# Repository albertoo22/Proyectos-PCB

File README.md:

# Proyectos-PCB
 In this folder I will publish my Hardware design projects. Some designed with KiCAD 6.0 and others with Altium Designer

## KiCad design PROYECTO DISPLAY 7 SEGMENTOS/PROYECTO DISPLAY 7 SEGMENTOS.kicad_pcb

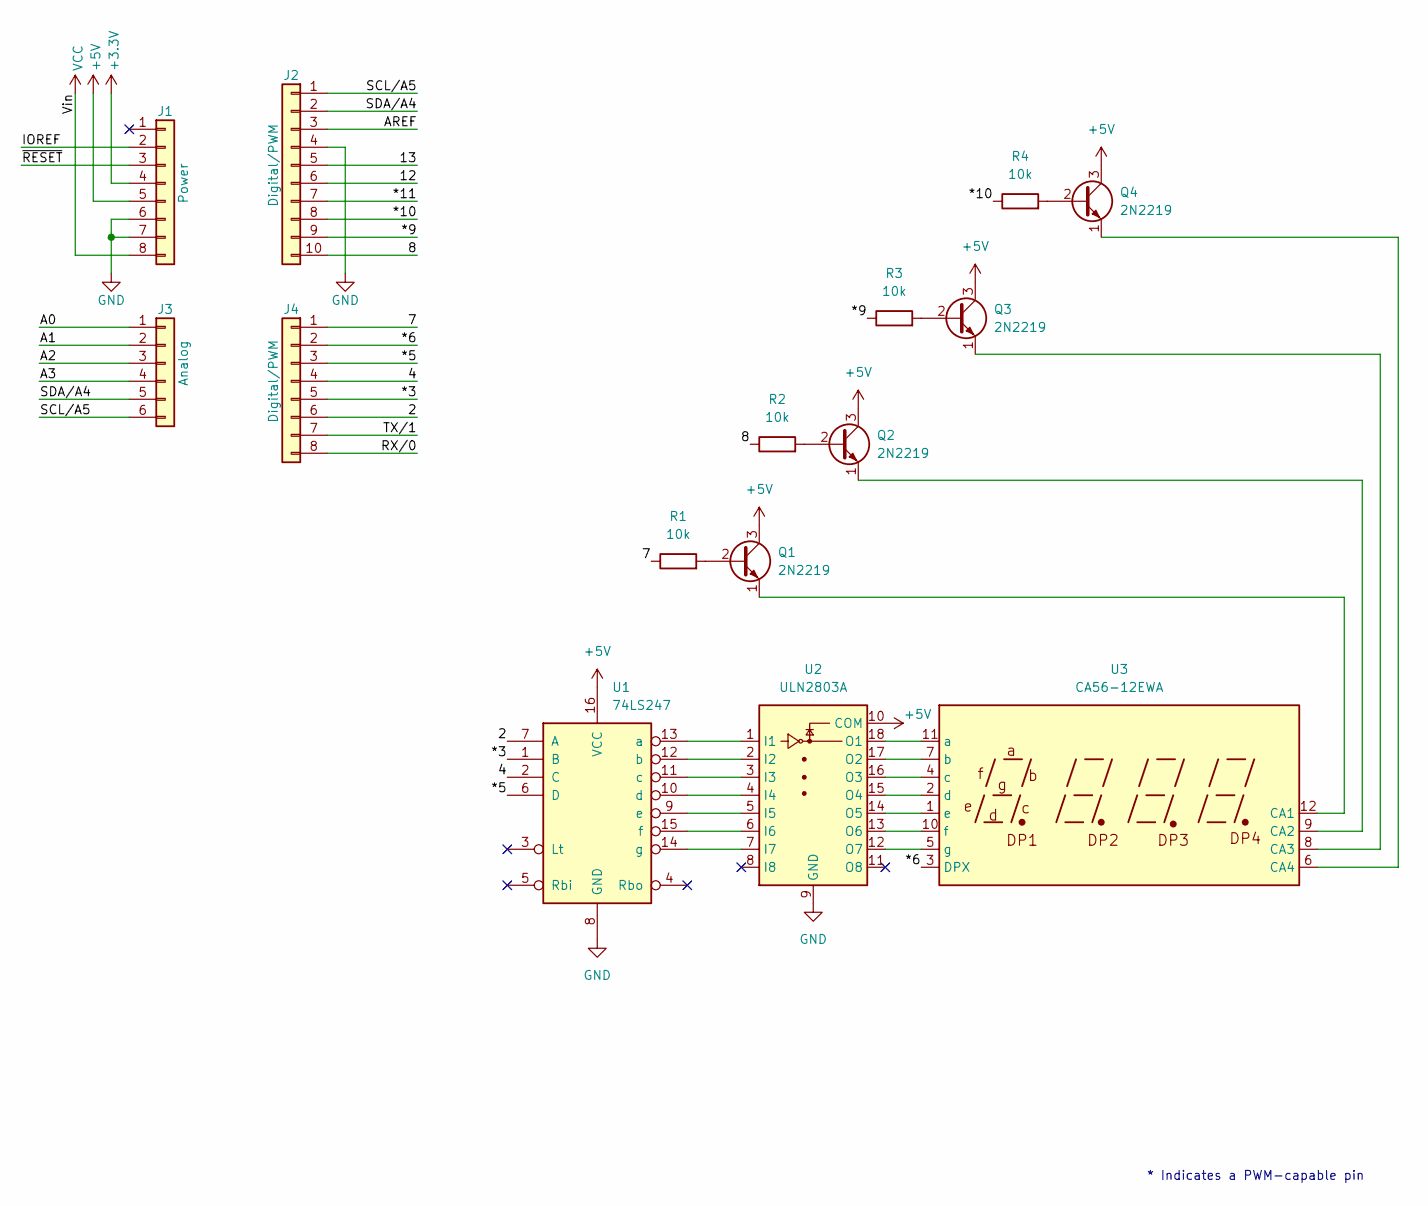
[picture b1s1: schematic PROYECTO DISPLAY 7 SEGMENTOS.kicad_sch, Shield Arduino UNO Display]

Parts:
J1: Power; PinSocket_1x08_P2.54mm_Vertical
J2: Digital/PWM; PinSocket_1x10_P2.54mm_Vertical
J3: Analog; PinSocket_1x06_P2.54mm_Vertical
J4: Digital/PWM; PinSocket_1x08_P2.54mm_Vertical
Q1, Q2, Q3, Q4: 2N2219; TO-39-3
R1, R2, R3, R4: 10k; R_2010_5025Metric
U1: 74LS247; DIP-16_W7.62mm
U2: ULN2803A; DIP-18_W7.62mm
U3: CA56-12EWA

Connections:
+3V3: J1.4
+5V: J1.5, Q1.3 (C), Q2.3 (C), Q3.3 (C), Q4.3 (C), U1.16 (VCC), U2.10 (COM)
/2: J4.6, U1.7 (A)
/4: J4.4, U1.2 (C)
/7: J4.1, R1.1
/8: J2.10, R2.1
/12: J2.6
/13: J2.5
/*3: J4.5, U1.1 (B)
/*5: J4.3, U1.6 (D)
/*6: J4.2, U3.3 (DPX)
/*9: J2.9, R3.1
/*10: J2.8, R4.1
/*11: J2.7
/A0: J3.1
/A1: J3.2
/A2: J3.3
/A3: J3.4
/AREF: J2.3
/IOREF: J1.2
/RX/0: J4.8
/SCL/A5: J2.1, J3.6
/SDA/A4: J2.2, J3.5
/TX/1: J4.7
/~RESET: J1.3
GND: J1.6, J1.7, J2.4, U1.8 (GND), U2.9 (GND)
unnamed: Q1.1 (E), U3.12 (CA1)
unnamed: Q1.2 (B), R1.2
unnamed: Q2.1 (E), U3.9 (CA2)
unnamed: Q2.2 (B), R2.2
unnamed: Q3.1 (E), U3.8 (CA3)
unnamed: Q3.2 (B), R3.2
unnamed: Q4.1 (E), U3.6 (CA4)
unnamed: Q4.2 (B), R4.2
unnamed: U1.9 (e), U2.5 (I5)
unnamed: U1.10 (d), U2.4 (I4)
unnamed: U1.11 (c), U2.3 (I3)
unnamed: U1.12 (b), U2.2 (I2)
unnamed: U1.13 (a), U2.1 (I1)
unnamed: U1.14 (g), U2.7 (I7)
unnamed: U1.15 (f), U2.6 (I6)
unnamed: U2.12 (O7), U3.5 (g)
unnamed: U2.13 (O6), U3.10 (f)
unnamed: U2.14 (O5), U3.1 (e)
unnamed: U2.15 (O4), U3.2 (d)
unnamed: U2.16 (O3), U3.4 (c)
unnamed: U2.17 (O2), U3.7 (b)
unnamed: U2.18 (O1), U3.11 (a)
VCC: J1.8

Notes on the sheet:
* Indicates a PWM-capable pin

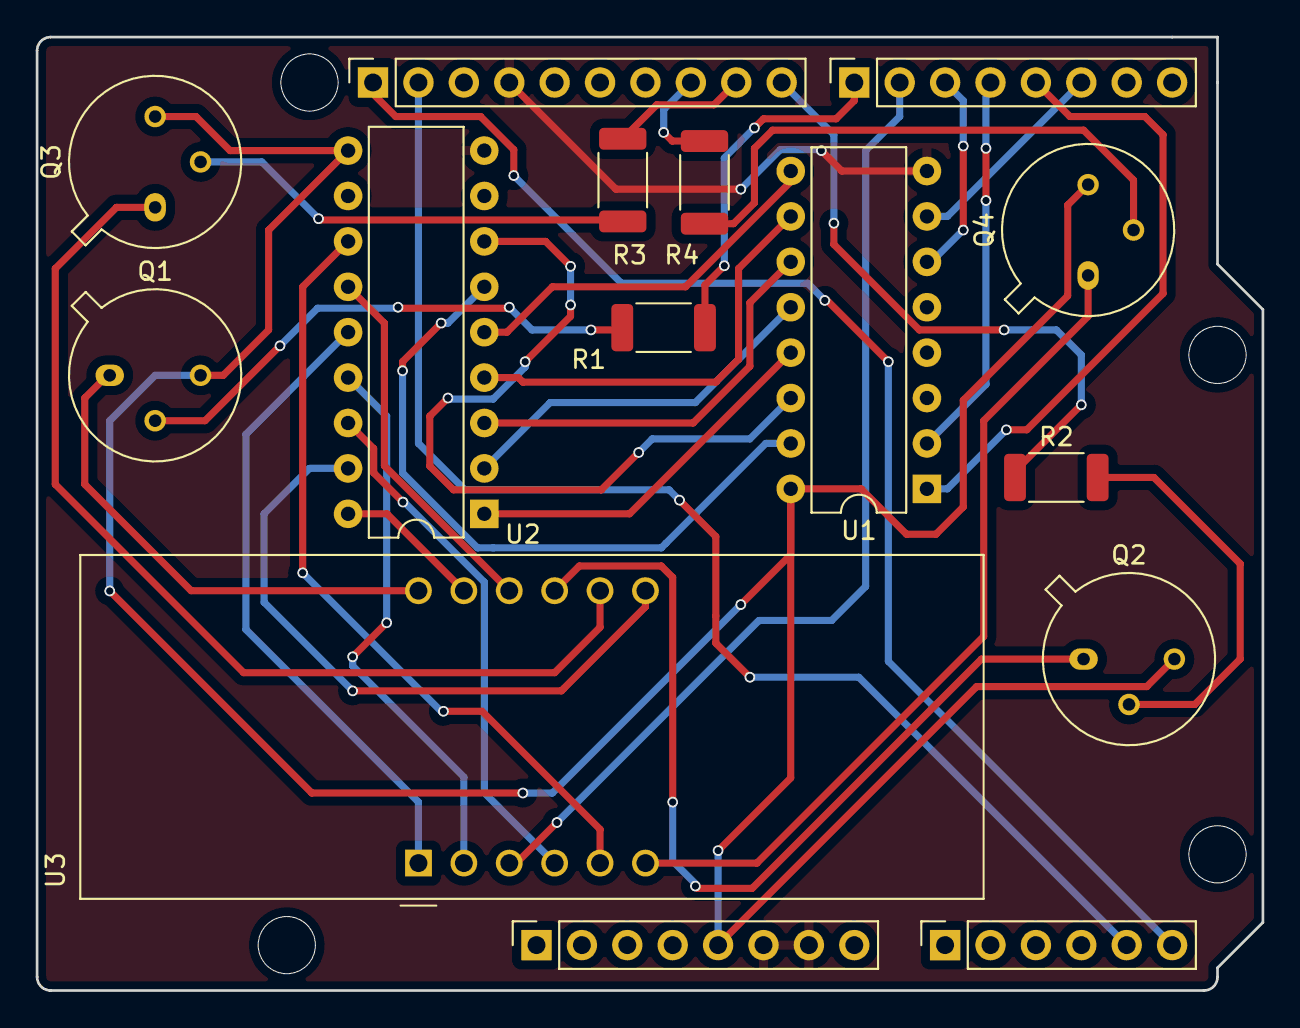
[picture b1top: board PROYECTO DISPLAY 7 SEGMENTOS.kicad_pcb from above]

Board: 2 copper layers, 68.6 x 53.3 mm, 19 parts (0 on the bottom side), 35 nets.

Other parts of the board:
MH1, MH2, MH3, MH4: MountingHole_3.2mm

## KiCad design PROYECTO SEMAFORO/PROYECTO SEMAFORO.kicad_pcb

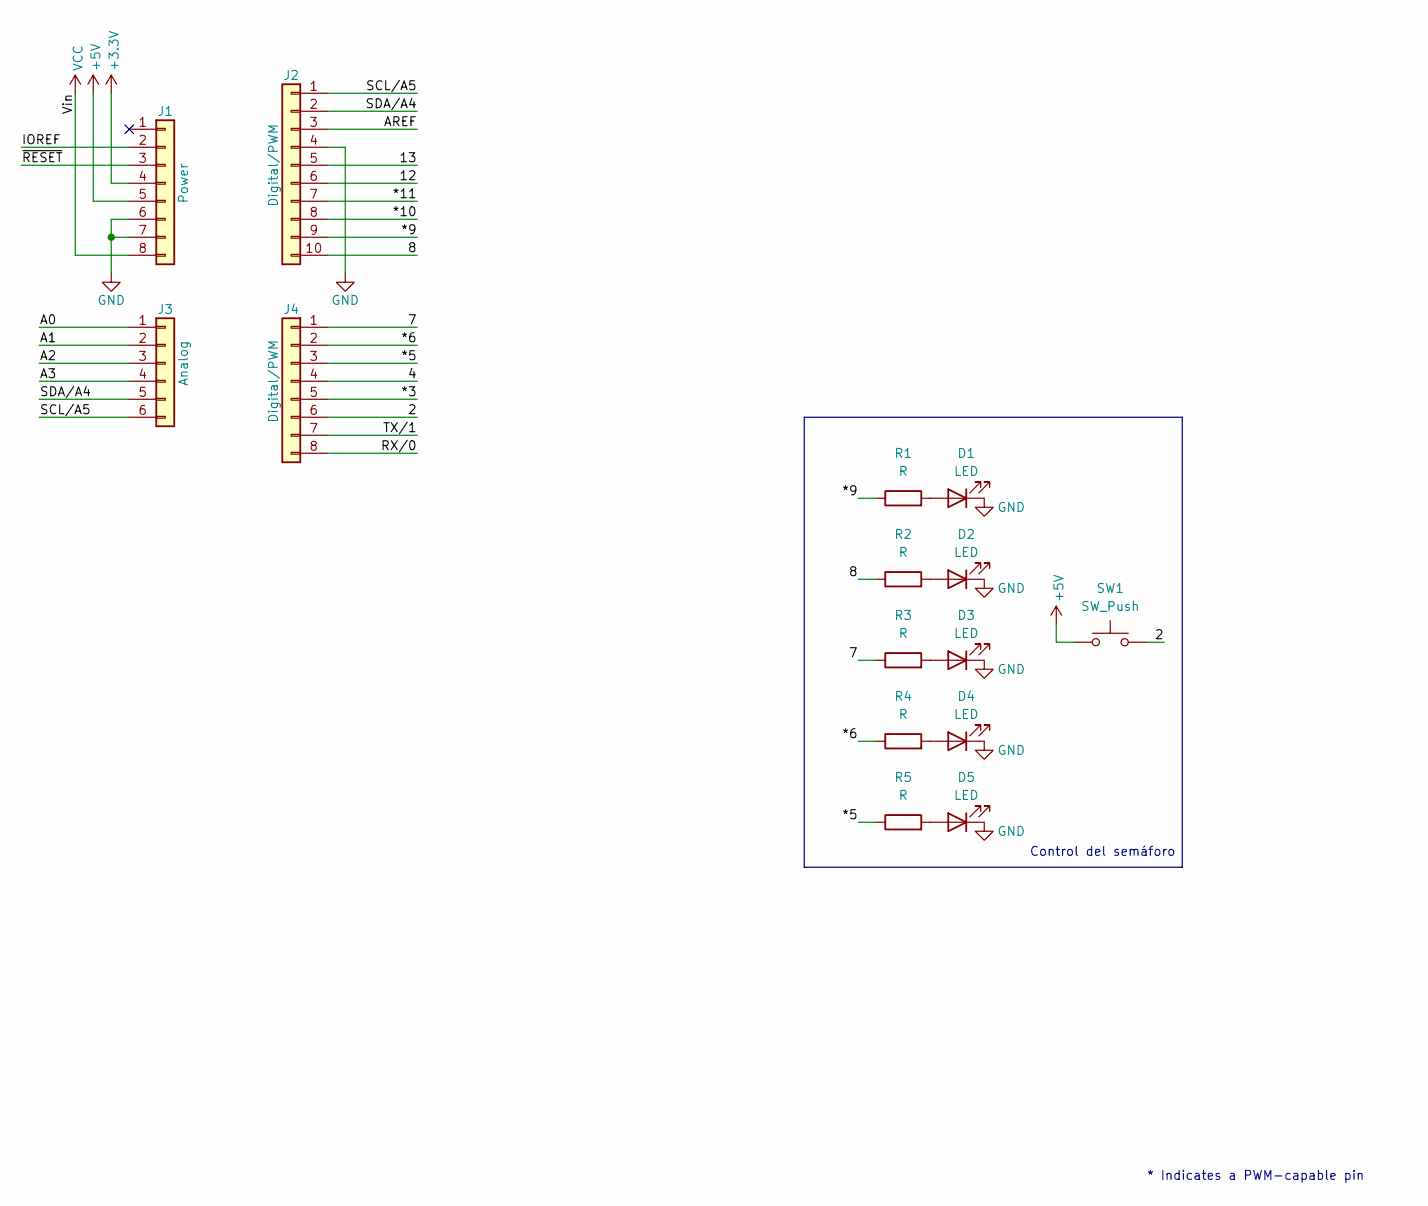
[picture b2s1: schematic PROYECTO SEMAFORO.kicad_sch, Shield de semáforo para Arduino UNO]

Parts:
D1, D2, D3: LED; LED_D3.0mm
D4, D5: LED; LED_D1.8mm_W3.3mm_H2.4mm
J1: Power; PinSocket_1x08_P2.54mm_Vertical
J2: Digital/PWM; PinSocket_1x10_P2.54mm_Vertical
J3: Analog; PinSocket_1x06_P2.54mm_Vertical
J4: Digital/PWM; PinSocket_1x08_P2.54mm_Vertical
R1, R2, R3, R4, R5: R; R_2010_5025Metric
SW1: SW_Push; SW_PUSH_6mm

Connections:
+3V3: J1.4
+5V: J1.5, SW1.1
/2: J4.6, SW1.2
/4: J4.4
/7: J4.1, R3.1
/8: J2.10, R2.1
/12: J2.6
/13: J2.5
/*3: J4.5
/*5: J4.3, R5.1
/*6: J4.2, R4.1
/*9: J2.9, R1.1
/*10: J2.8
/*11: J2.7
/A0: J3.1
/A1: J3.2
/A2: J3.3
/A3: J3.4
/AREF: J2.3
/IOREF: J1.2
/RX/0: J4.8
/SCL/A5: J2.1, J3.6
/SDA/A4: J2.2, J3.5
/TX/1: J4.7
/~RESET: J1.3
GND: D1.1 (K), D2.1 (K), D3.1 (K), D4.1 (K), D5.1 (K), J1.6, J1.7, J2.4
unnamed: D1.2 (A), R1.2
unnamed: D2.2 (A), R2.2
unnamed: D3.2 (A), R3.2
unnamed: D4.2 (A), R4.2
unnamed: D5.2 (A), R5.2
VCC: J1.8

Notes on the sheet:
Control del semáforo
* Indicates a PWM-capable pin

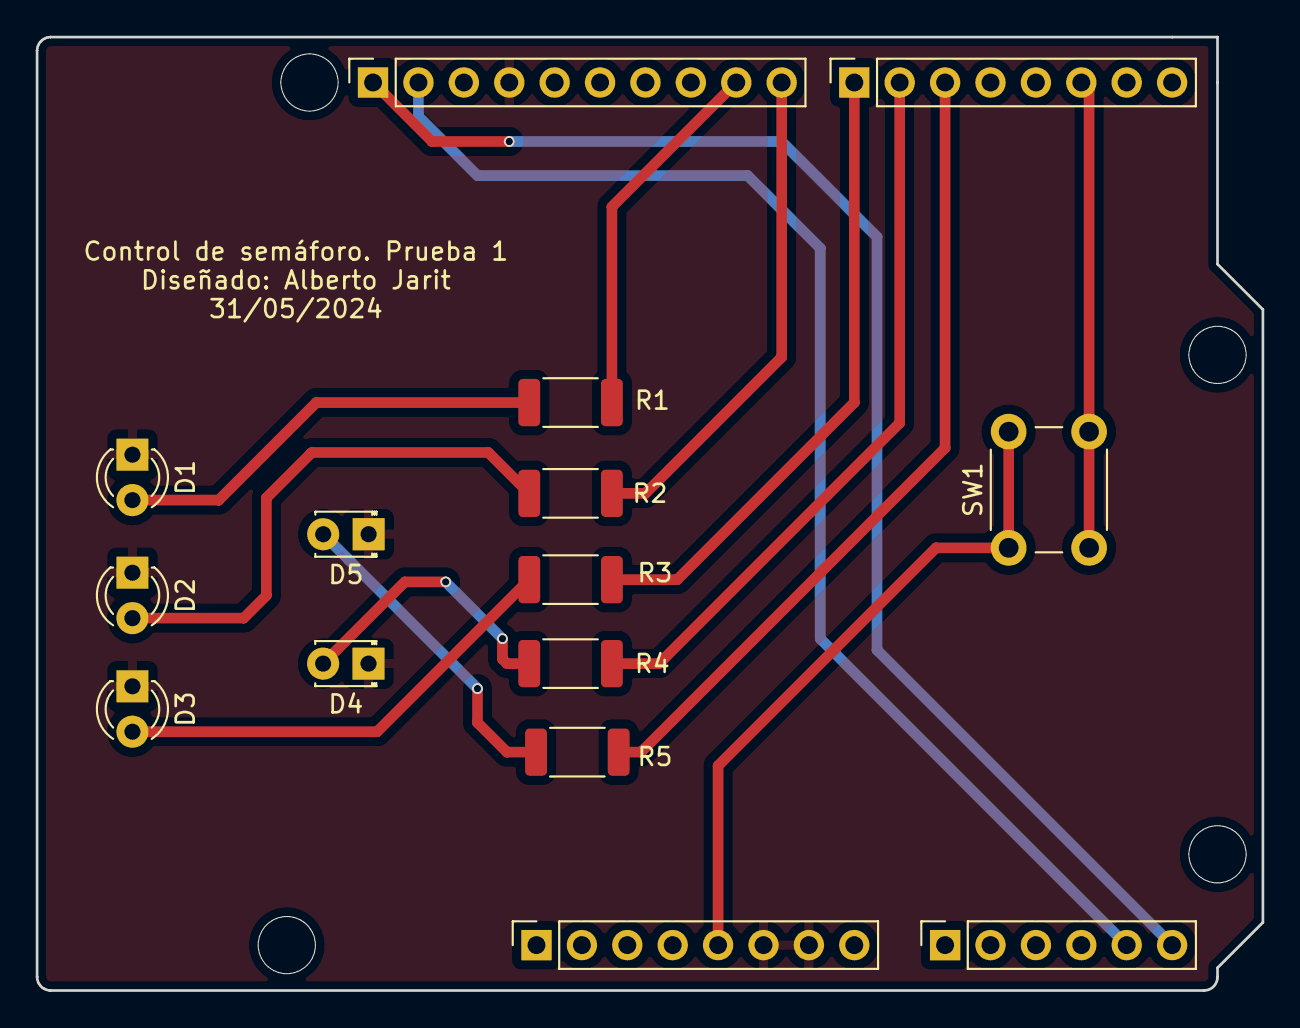
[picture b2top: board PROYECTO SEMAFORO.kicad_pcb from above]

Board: 2 copper layers, 68.6 x 53.3 mm, 19 parts (0 on the bottom side), 15 nets.

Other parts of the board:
MH1, MH2, MH3, MH4: MountingHole_3.2mm

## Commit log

2024-06-01 Create Code
